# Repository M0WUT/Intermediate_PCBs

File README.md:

# Intermediate_PCBs
Selection of PCBs designed to help with the UK Intermediate Amateur Radio Licence practical requirements

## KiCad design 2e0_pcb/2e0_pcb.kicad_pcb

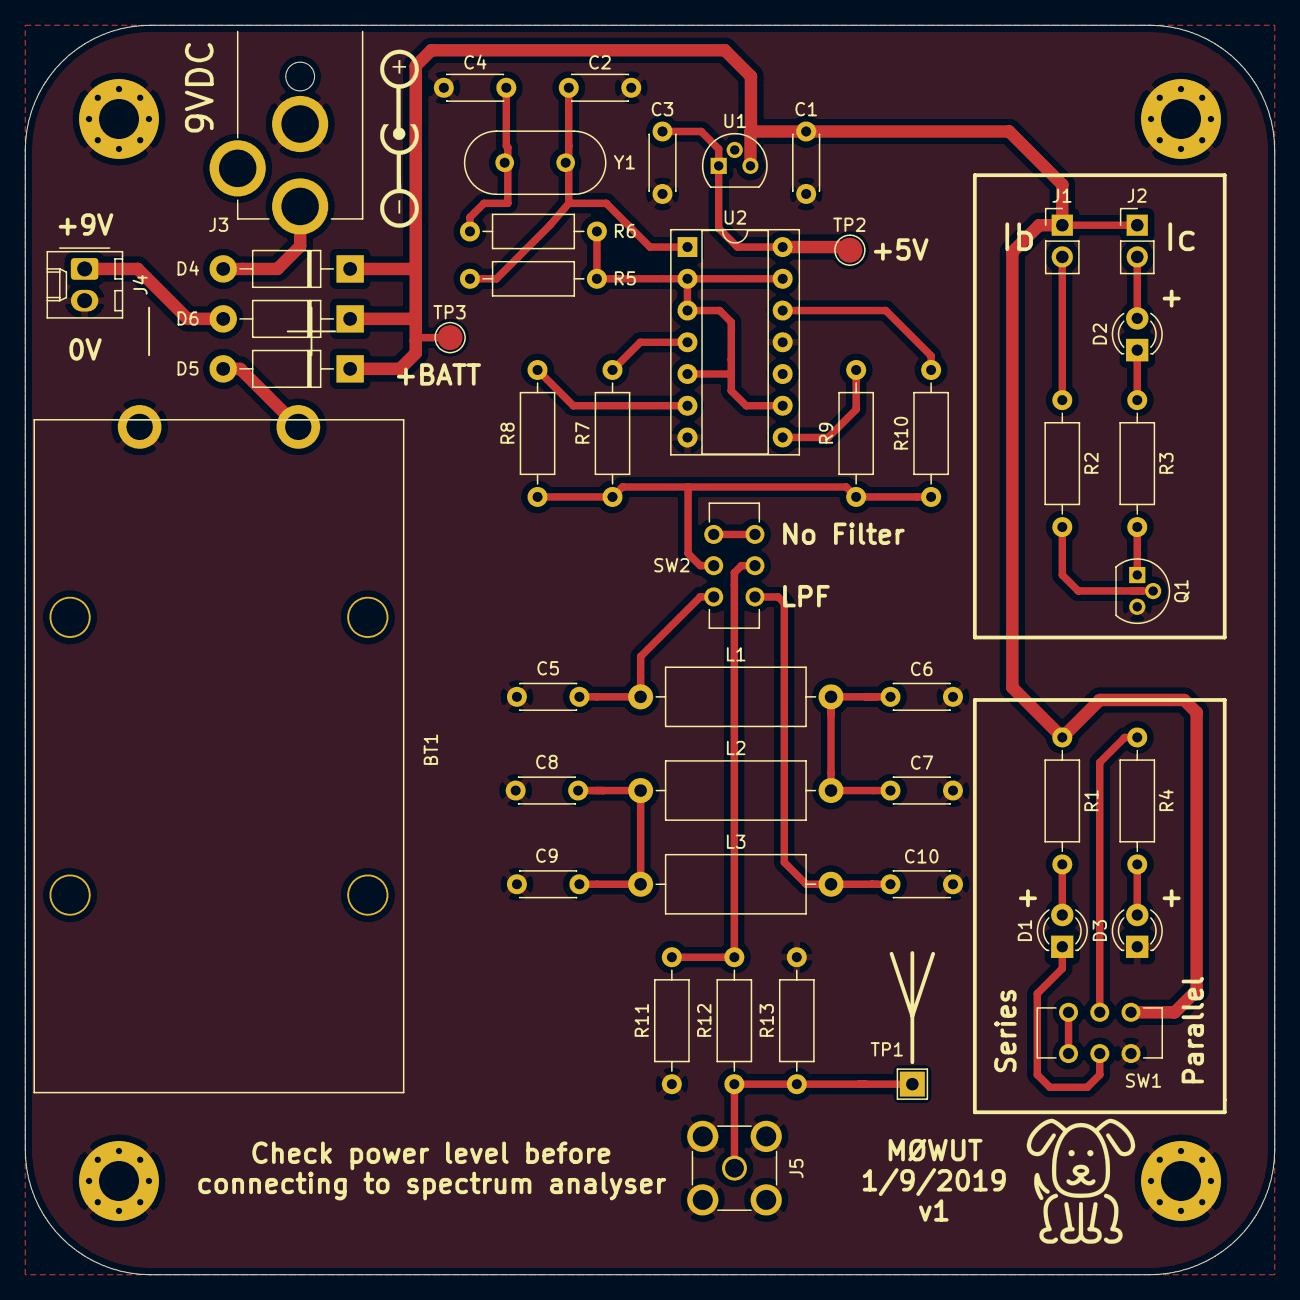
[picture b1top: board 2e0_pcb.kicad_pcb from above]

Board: 2 copper layers, 100.0 x 100.0 mm, 53 parts (0 on the bottom side), 31 nets.

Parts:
BT1: Battery; Battery_PP3_Keystone_1294_TH
C1, C3: 1uF; C_Disc_D4.3mm_W1.9mm_P5.00mm
C2, C4: 10p; C_Disc_D4.3mm_W1.9mm_P5.00mm
C5, C10: 680p; C_Disc_D4.3mm_W1.9mm_P5.00mm
C6, C8: 330p; C_Disc_D4.3mm_W1.9mm_P5.00mm
C7, C9: 1n; C_Disc_D4.3mm_W1.9mm_P5.00mm
D1, D2, D3: HLMP-1521; LED_D3.0mm
D4, D5, D6: 1N5818; D_DO-41_SOD81_P10.16mm_Horizontal
H1, H2, H3, H4: Pad; MountingHole_3.2mm_M3_Pad_Via
J1, J2: Conn_01x02; PinHeader_1x02_P2.54mm_Vertical
J3: Jack-DC; Barrel-Jack_Cliff_FC681478_TH
J4: Conn_01x02; Molex_KK-254_AE-6410-02A_1x02_P2.54mm_Vertical
J5: Conn_Coaxial; SMA_TE_5-1814832-1_Vertical
L1, L2, L3: 3u3; L_Axial_L11.0mm_D4.5mm_P15.24mm_Horizontal_Fastron_MECC
M1: Barrel_Polarity
M2: Logo_10mmx10mm
Q1: BC547CBU; TO-92L
R1, R4, R12: 680R; R_Axial_DIN0207_L6.3mm_D2.5mm_P10.16mm_Horizontal
R2: 150k; R_Axial_DIN0207_L6.3mm_D2.5mm_P10.16mm_Horizontal
R3: 330; R_Axial_DIN0207_L6.3mm_D2.5mm_P10.16mm_Horizontal
R5: 1M; R_Axial_DIN0207_L6.3mm_D2.5mm_P10.16mm_Horizontal
R6: 3k9; R_Axial_DIN0207_L6.3mm_D2.5mm_P10.16mm_Horizontal
R7, R8, R9, R10: 200R; R_Axial_DIN0207_L6.3mm_D2.5mm_P10.16mm_Horizontal
R11, R13: 51R; R_Axial_DIN0207_L6.3mm_D2.5mm_P10.16mm_Horizontal
SW1, SW2: SW_DPDT_x2; C+K_Slide_DPDT_JS202011CQN_TH
TP1: TestPoint; TestPoint_THTPad_2.0x2.0mm_Drill1.0mm
TP2, TP3: TestPoint; TestPoint_Pad_D2.0mm
U1: L78L05_TO92; TO-92L
U2: 74HC04; DIP-14_W7.62mm_Socket
Y1: 3.58MHz; Crystal_HC49-U_Vertical

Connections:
+5V: C3.1, TP2.1, U1.1, U2.14
+BATT: C1.1, D4.1, D5.1, D6.1, J1.1, J2.1, R1.1, SW1.6, TP3.1, U1.3
GND: BT1.2, C1.2, C2.2, C3.2, C4.2, C5.2, C6.2, C7.2, C8.2, C9.2, C10.2, D3.1, H1.1, H2.1, H3.1, H4.1, J3.2, J4.2, J5.2, Q1.3, R11.1, R13.2, SW1.3, U1.2, U2.7, U2.11
unnamed: BT1.1, D5.2
unnamed: C2.1, R5.2, U2.1, Y1.1
unnamed: C4.1, R6.2, Y1.2
unnamed: C5.1, L1.1, SW2.3
unnamed: C6.1, C7.1, L1.2, L2.2
unnamed: C8.1, C9.1, L2.1, L3.1
unnamed: C10.1, L3.2, SW2.6
unnamed: D1.1, SW1.2
unnamed: D1.2, R1.2
unnamed: D2.1, R3.1
unnamed: D2.2, J2.2
unnamed: D3.2, R4.2
unnamed: D4.2, J3.1
unnamed: D6.2, J4.1
unnamed: J1.2, R2.1
unnamed: J5.1, R12.1, R13.1, TP1.1
unnamed: Q1.1, R3.2
unnamed: Q1.2, R2.2
unnamed: R4.1, SW1.5
unnamed: R5.1, R6.1, U2.2, U2.3, U2.5, U2.9, U2.13
unnamed: R7.2, U2.4
unnamed: R8.2, U2.6
unnamed: R9.2, U2.8
unnamed: R7.1, R8.1, R9.1, R10.1, SW2.2
unnamed: R10.2, U2.12
unnamed: R11.2, R12.2, SW2.5
unnamed: SW1.1, SW1.4
unnamed: SW2.1, SW2.4

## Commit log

2019-08-29 First draft
    Still not sure what qualifies as one section says "Make a circuit that shows..." Guessing a pre-made board doesn't count
2019-08-30 first draft complete
2019-08-30 minor aesthetic updates
2019-08-30 stopped input pin from floating
2019-09-01 Release 1
    Boards ordered 1/9/2018
2019-10-28 Added changes from testing
2019-10-28 added documentation
2019-11-06 added PDF schematic
